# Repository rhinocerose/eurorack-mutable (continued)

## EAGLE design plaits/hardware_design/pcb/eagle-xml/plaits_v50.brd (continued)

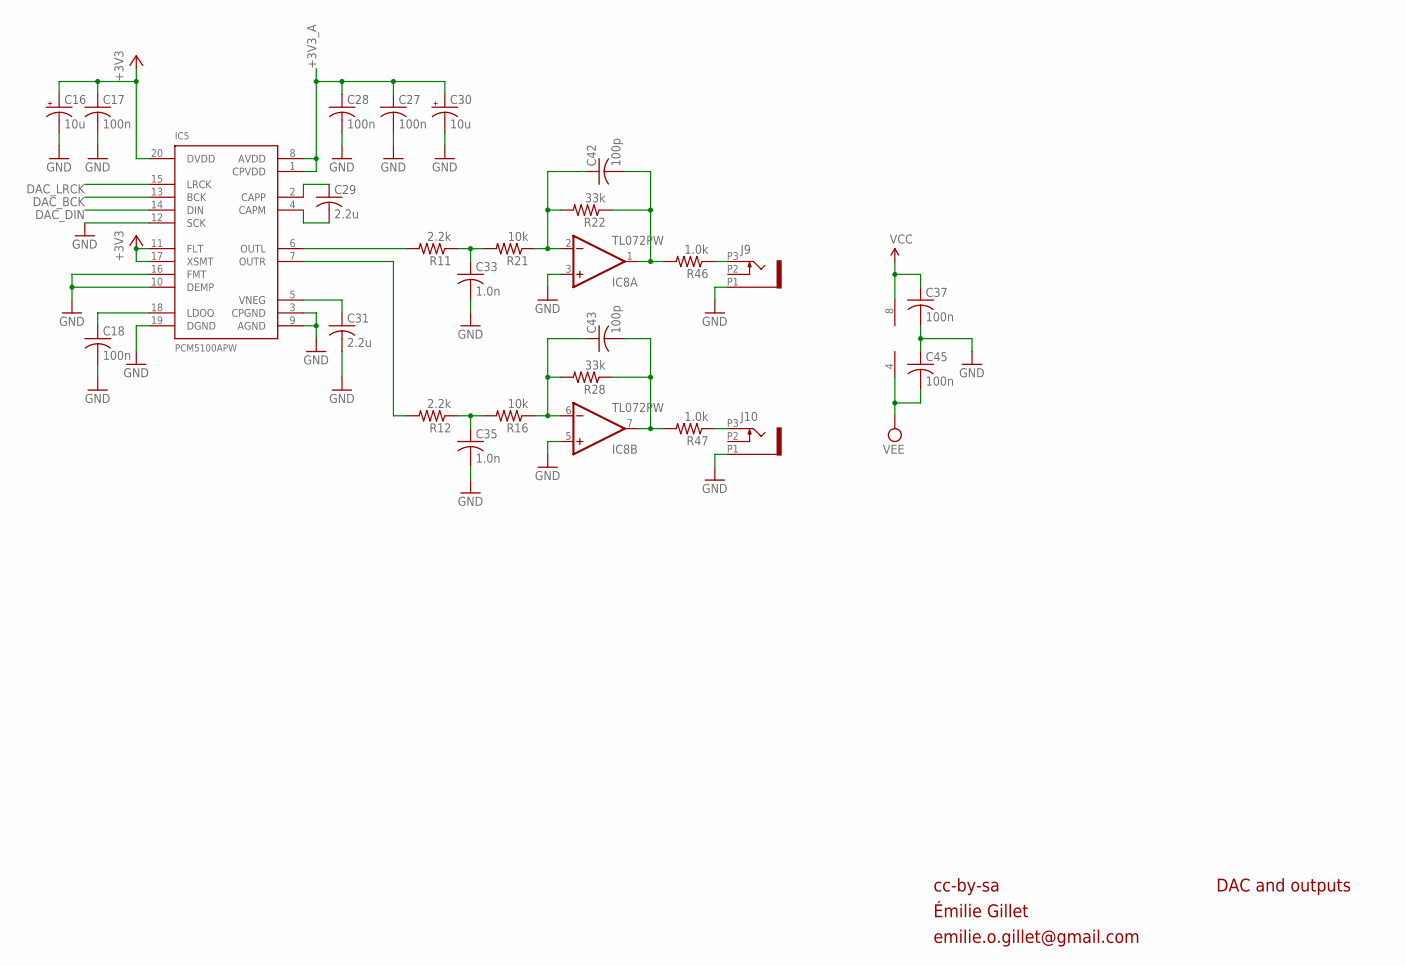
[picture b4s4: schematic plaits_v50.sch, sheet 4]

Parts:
C16, C30: 10u; PANASONIC_A
C17, C18, C27, C28, C37, C45: 100n; C0402
C29, C31: 2.2u; C0805
C33, C35: 1.0n; C0402
C42, C43: 100p; C0402
IC5: PCM5100APW; SSOP20
IC8: TL072PW; TSSOP08
J9, J10: PJ301_THONKICONN6; WQP_PJ_301M6
R11, R12: 2.2k; R0402
R16, R21: 10k; R0402
R22, R28: 33k; R0402
R46, R47: 1.0k; R0603

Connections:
+3V3: C16.+, C17.1, IC5.11 (FLT), IC5.17 (XSMT), IC5.20 (DVDD); also elsewhere on the board
+3V3_A: C27.1, C28.1, C30.+, IC5.1 (CPVDD), IC5.8 (AVDD); also elsewhere on the board
DAC_BCK: IC5.13 (BCK); also elsewhere on the board
DAC_DIN: IC5.14 (DIN); also elsewhere on the board
DAC_LRCK: IC5.15 (LRCK); also elsewhere on the board
GND: C16.-, C17.2, C18.2, C27.2, C28.2, C30.-, C31.2, C33.2, C35.2, C37.2, C45.1, IC5.3 (CPGND), IC5.9 (AGND), IC5.10 (DEMP), IC5.12 (SCK), IC5.16 (FMT), IC5.19 (DGND), IC8.3 (+IN), IC8.5 (+IN), J9.P1 (1), J10.P1 (1); also elsewhere on the board
unnamed: C29.1, IC5.2 (CAPP)
unnamed: C29.2, IC5.4 (CAPM)
unnamed: IC5.6 (OUTL), R11.2
unnamed: C33.1, R11.1, R21.2
unnamed: C35.1, R12.1, R16.2
unnamed: C31.1, IC5.5 (VNEG)
unnamed: C18.1, IC5.18 (LDOO)
unnamed: IC5.7 (OUTR), R12.2
unnamed: C43.1, IC8.6 (-IN), R16.1, R28.2
unnamed: C43.2, IC8.7 (OUT), R28.1, R47.2
unnamed: C42.1, IC8.2 (-IN), R21.1, R22.2
unnamed: C42.2, IC8.1 (OUT), R22.1, R46.2
unnamed: J9.P3 (3), R46.1
unnamed: J10.P3 (3), R47.1
VCC: C37.1, IC8.8 (V+); also elsewhere on the board
VEE: C45.2, IC8.4 (V-); also elsewhere on the board

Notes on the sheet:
cc-by-sa
DAC and outputs
Émilie Gillet
emilie.o.gillet@gmail.com

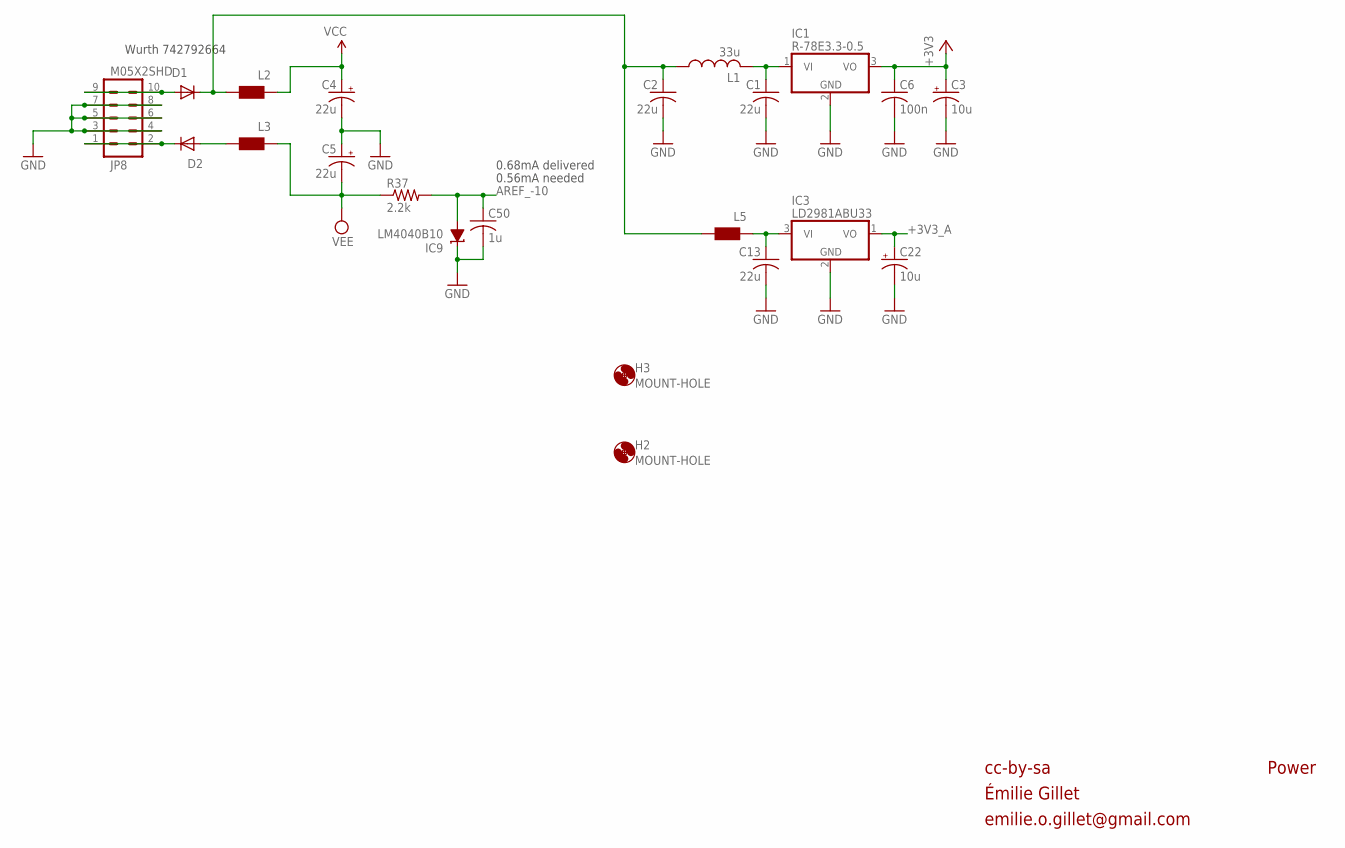
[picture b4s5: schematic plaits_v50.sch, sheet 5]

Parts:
C1, C2, C13: 22u; C1206
C3, C22: 10u; PANASONIC_A
C4, C5: 22u; PANASONIC_B
C6: 100n; C0402
C50: 1u; C0402
D1, D2: 1N5819HW; SOD123
H2, H3: MOUNT-HOLE; 3,0TINY
IC1: R-78E3.3-0.5; WE78
IC3: LD2981ABU33; SOT89
IC9: LM4040B10; DBZ_R-PDSO-G3
JP8: M05X2SHD; 2X5-SHROUDED
L1: 33u; L2012C
L2, L3, L5: WE-CBF_0603; 0603
R37: 2.2k; R0402

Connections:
+3V3: C3.+, C6.1, IC1.3 (VO); also elsewhere on the board
+3V3_A: C22.+, IC3.1 (VO); also elsewhere on the board
AREF_-10: C50.1, IC9.2 (A), R37.2; also elsewhere on the board
GND: C1.2, C2.2, C3.-, C4.-, C5.+, C6.2, C13.2, C22.-, C50.2, IC1.2 (GND), IC3.2 (GND), IC9.1 (C), JP8.3, JP8.4, JP8.5, JP8.6, JP8.7, JP8.8; also elsewhere on the board
unnamed: C1.1, IC1.1 (VI), L1.2
unnamed: D2.A, L3.2
unnamed: C2.1, D1.C, L1.1, L2.2, L5.2
unnamed: C13.1, IC3.3 (VI), L5.1
unnamed: D1.A, JP8.9, JP8.10
unnamed: D2.C, JP8.1, JP8.2
VCC: C4.+, L2.1; also elsewhere on the board
VEE: C5.-, L3.1, R37.1; also elsewhere on the board

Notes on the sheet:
cc-by-sa
Power
0.56mA needed
Wurth 742792664
0.68mA delivered
Émilie Gillet
emilie.o.gillet@gmail.com

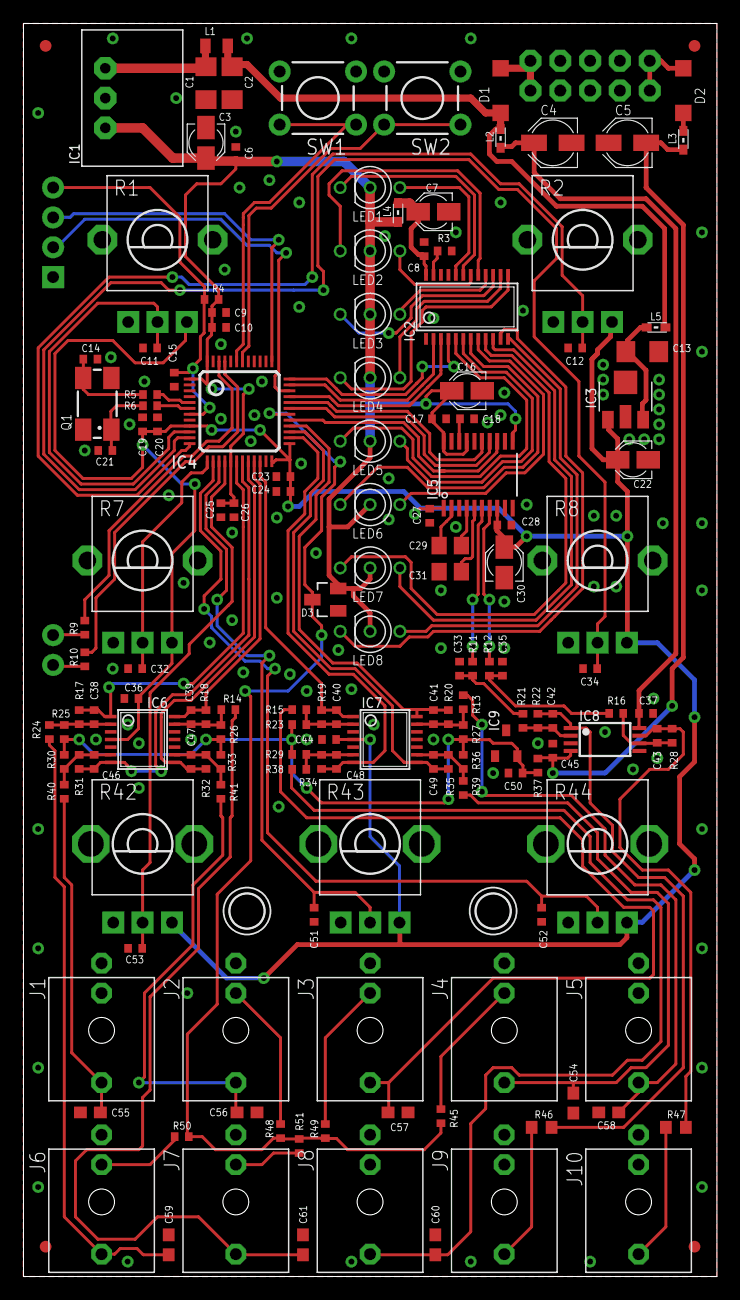
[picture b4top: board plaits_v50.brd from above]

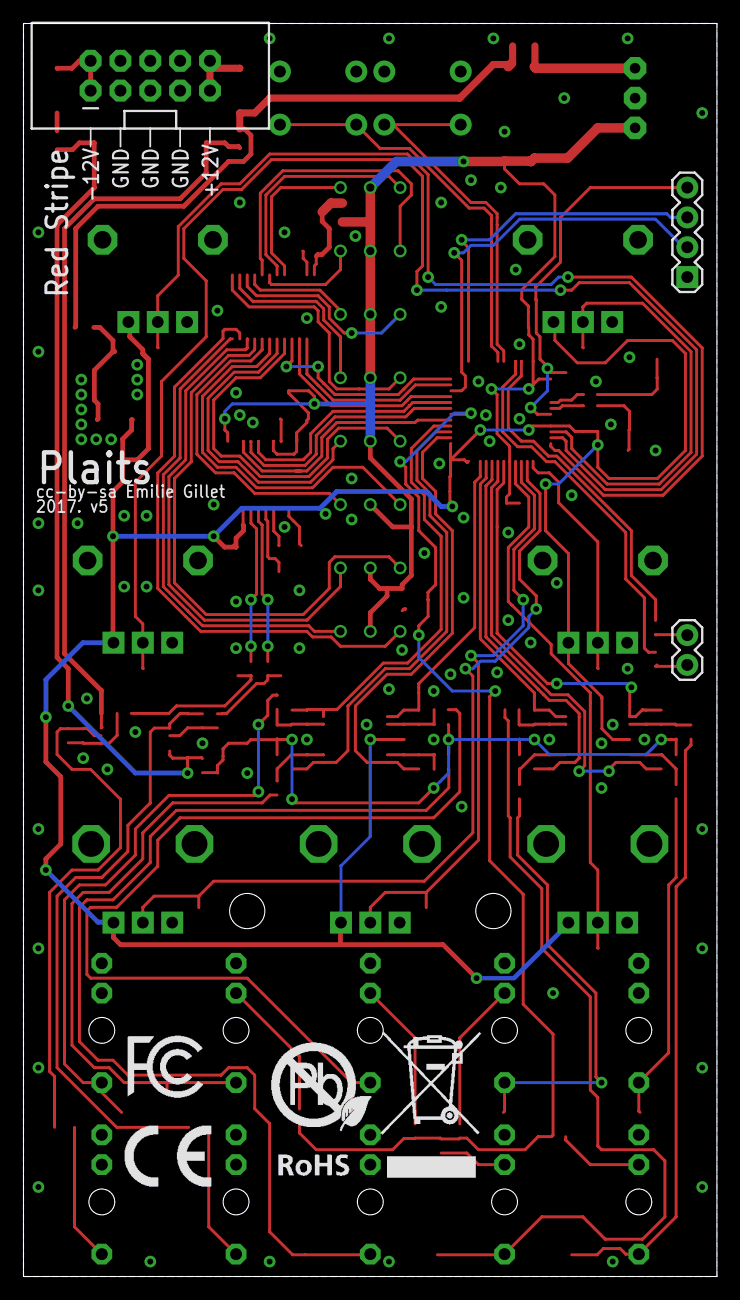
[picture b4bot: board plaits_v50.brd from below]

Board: 2 copper layers, 59.0 x 106.7 mm, 162 parts (6 on the bottom side), 100 nets.

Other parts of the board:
U$1: FCC_MEDIUM
U$2: ROHS_BIG
U$3: CE_MEDIUM

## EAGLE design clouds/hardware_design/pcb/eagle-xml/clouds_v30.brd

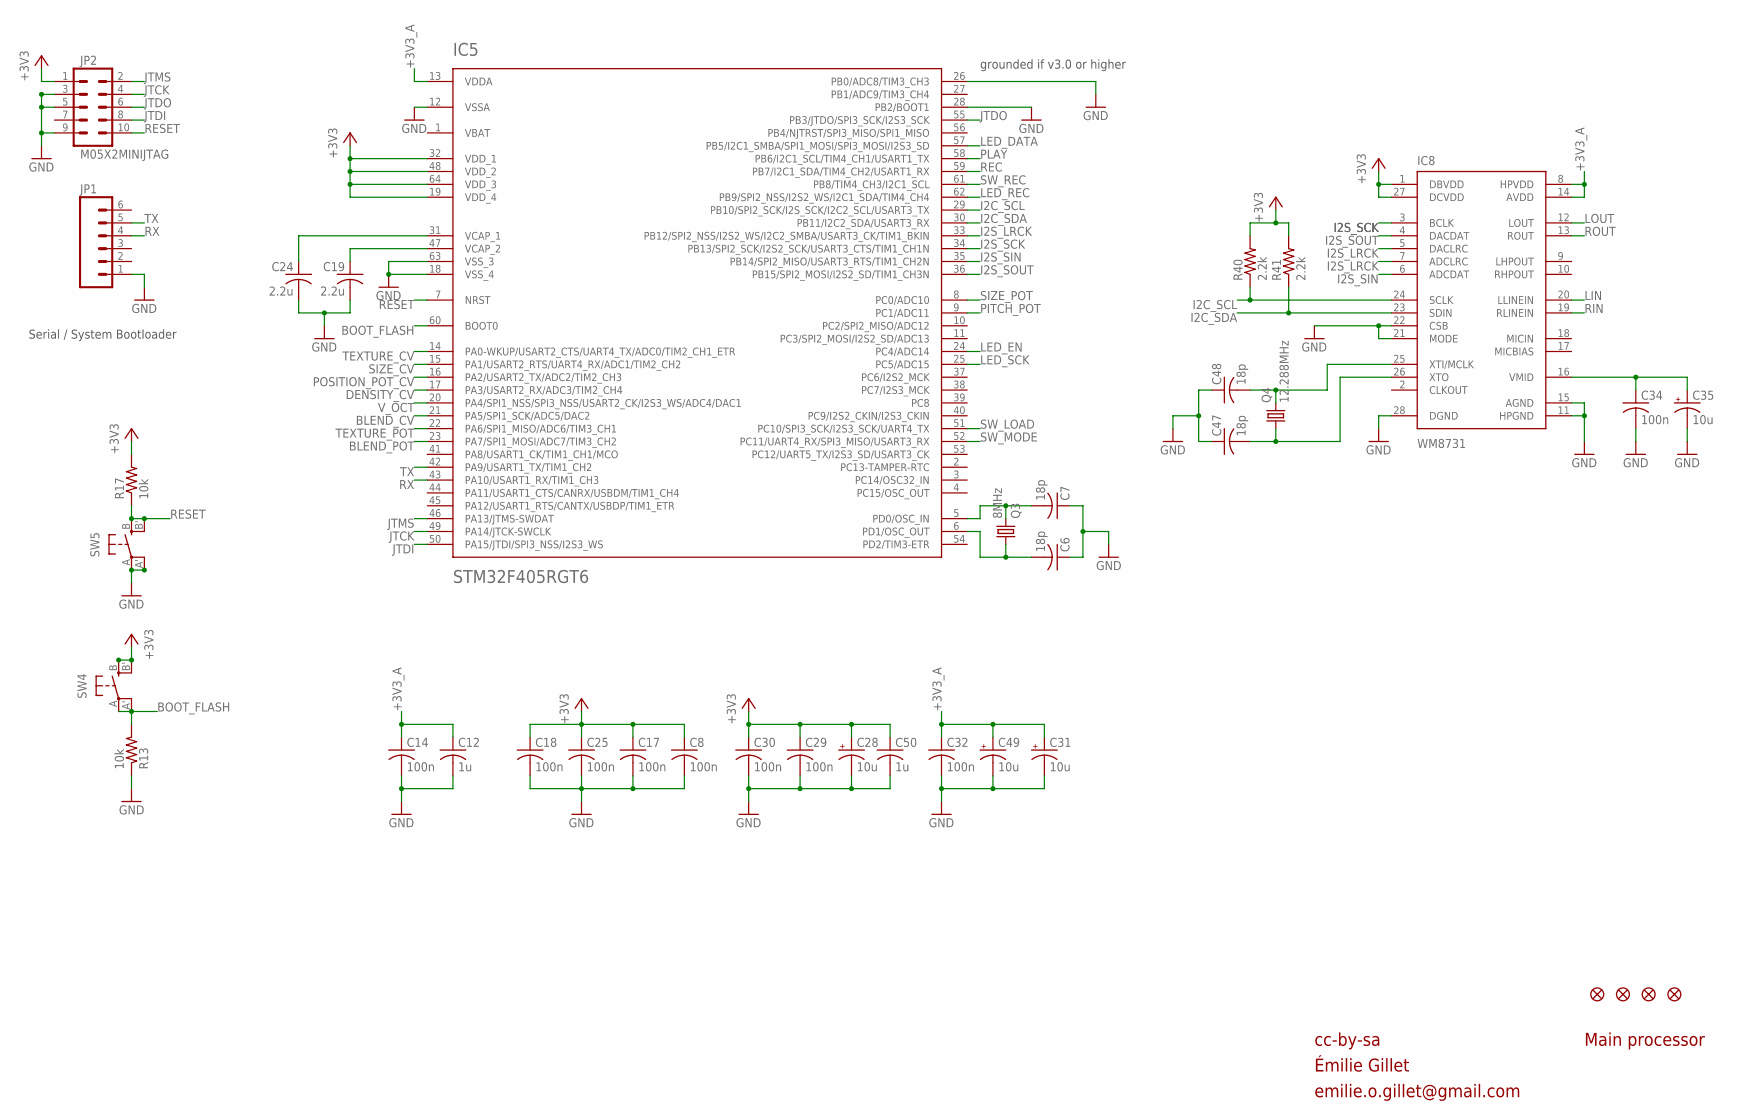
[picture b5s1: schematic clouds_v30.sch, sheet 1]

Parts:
C6, C7, C47, C48: 18p; C0603
C8, C14, C17, C18, C25, C29, C30, C32, C34: 100n; C0603
C12, C50: 1u; C0603
C19, C24: 2.2u; C0805
C28, C49: 10u; PANASONIC_A
C31, C35: 10u; PANASONIC_B
F1, F2, F3, F4: FIDUCIAL1X2; FIDUCIAL-1X2
IC5: STM32F405RGT6; TQFP-10X10-64
IC8: WM8731; SSOP28
JP1: M06SIP; 1X06
JP2: M05X2MINIJTAG; 2X5-1.27
Q3: 8MHz; HC49UP
Q4: 12.288MHz; HC49UP
R13, R17: 10k; R0603
R40, R41: 2.2k; R0603
SW4, SW5: EVQQ2; EVQ-Q2

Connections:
+3V3: C8.1, C17.1, C18.1, C25.1, C28.+, C29.1, C30.1, C50.1, IC5.19 (VDD_4), IC5.32 (VDD_1), IC5.48 (VDD_2), IC5.64 (VDD_3), IC8.1 (DBVDD), IC8.27 (DCVDD), JP2.1, R17.2, R40.2, R41.2, SW4.B (S), SW4.B' (S1); also elsewhere on the board
+3V3_A: C12.1, C14.1, C31.+, C32.1, C49.+, IC5.13 (VDDA), IC8.8 (HPVDD), IC8.14 (AVDD); also elsewhere on the board
BLEND_CV: IC5.21 (PA5/SPI1_SCK/ADC5/DAC2); also elsewhere on the board
BLEND_POT: IC5.23 (PA7/SPI1_MOSI/ADC7/TIM3_CH2); also elsewhere on the board
BOOT_FLASH: IC5.60 (BOOT0), R13.2, SW4.A, SW4.A' (P1)
DENSITY_CV: IC5.17 (PA3/USART2_RX/ADC3/TIM2_CH4); also elsewhere on the board
GND: C6.1, C7.1, C8.2, C12.2, C14.2, C17.2, C18.2, C19.2, C24.2, C25.2, C28.-, C29.2, C30.2, C31.-, C32.2, C34.2, C35.-, C47.1, C48.1, C49.-, C50.2, IC5.12 (VSSA), IC5.18 (VSS_4), IC5.26 (PB0/ADC8/TIM3_CH3), IC5.28 (PB2/BOOT1), IC5.63 (VSS_3), IC8.11 (HPGND), IC8.15 (AGND), IC8.21 (MODE), IC8.22 (CSB), IC8.28 (DGND), JP1.1, JP2.3, JP2.5, JP2.9, R13.1, SW5.A, SW5.A' (P1); also elsewhere on the board
I2C_SCL: IC5.29 (PB10/SPI2_SCK/I2S_SCK/I2C2_SCL/USART3_TX), IC8.24 (SCLK), R40.1
I2C_SDA: IC5.30 (PB11/I2C2_SDA/USART3_RX), IC8.23 (SDIN), R41.1
I2S_LRCK: IC5.33 (PB12/SPI2_NSS/I2S2_WS/I2C2_SMBA/USART3_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), IC8.5 (DACLRC), IC8.7 (ADCLRC)
I2S_SCK: IC5.34 (PB13/SPI2_SCK/I2S2_SCK/USART3_CTS/TIM1_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), IC8.3 (BCLK)
I2S_SIN: IC5.35 (PB14/SPI2_MISO/USART3_RTS/TIM1_CH2N), IC8.6 (ADCDAT)
I2S_SOUT: IC5.36 (PB15/SPI2_MOSI/I2S2_SD/TIM1_CH3N), IC8.4 (DACDAT)
JTCK: IC5.49 (PA14/JTCK-SWCLK), JP2.4
JTDI: IC5.50 (PA15/JTDI/SPI3_NSS/I2S3_WS), JP2.8
JTDO: IC5.55 (PB3/JTDO/SPI3_SCK/I2S3_SCK), JP2.6
JTMS: IC5.46 (PA13/JTMS-SWDAT), JP2.2
LED_DATA: IC5.57 (PB5/I2C1_SMBA/SPI1_MOSI/SPI3_MOSI/I2S3_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); also elsewhere on the board
LED_EN: IC5.24 (PC4/ADC14); also elsewhere on the board
LED_REC: IC5.62 (PB9/SPI2_NSS/I2S2_WS/I2C1_SDA/TIM4_CH4); also elsewhere on the board
LED_SCK: IC5.25 (PC5/ADC15); also elsewhere on the board
LIN: IC8.20 (LLINEIN); also elsewhere on the board
LOUT: IC8.12 (LOUT); also elsewhere on the board
unnamed: C7.2, IC5.5 (PD0/OSC_IN), Q3.2
unnamed: C6.2, IC5.6 (PD1/OSC_OUT), Q3.1
unnamed: C19.1, IC5.47 (VCAP_2)
unnamed: C34.1, C35.+, IC8.16 (VMID)
unnamed: C24.1, IC5.31 (VCAP_1)
unnamed: C47.2, IC8.26 (XTO), Q4.1
unnamed: C48.2, IC8.25 (XTI/MCLK), Q4.2
PITCH_POT: IC5.9 (PC1/ADC11); also elsewhere on the board
PLAY: IC5.58 (PB6/I2C1_SCL/TIM4_CH1/USART1_TX); also elsewhere on the board
POSITION_POT_CV: IC5.16 (PA2/USART2_TX/ADC2/TIM2_CH3); also elsewhere on the board
REC: IC5.59 (PB7/I2C1_SDA/TIM4_CH2/USART1_RX); also elsewhere on the board
RESET: IC5.7 (NRST), JP2.10, R17.1, SW5.B (S), SW5.B' (S1)
RIN: IC8.19 (RLINEIN); also elsewhere on the board
ROUT: IC8.13 (ROUT); also elsewhere on the board
RX: IC5.43 (PA10/USART1_RX/TIM1_CH3), JP1.4
SIZE_CV: IC5.15 (PA1/USART2_RTS/UART4_RX/ADC1/TIM2_CH2); also elsewhere on the board
SIZE_POT: IC5.8 (PC0/ADC10); also elsewhere on the board
SW_LOAD: IC5.51 (PC10/SPI3_SCK/I2S3_SCK/UART4_TX); also elsewhere on the board
SW_MODE: IC5.52 (PC11/UART4_RX/SPI3_MISO/USART3_RX); also elsewhere on the board
SW_REC: IC5.61 (PB8/TIM4_CH3/I2C1_SCL); also elsewhere on the board
TEXTURE_CV: IC5.14 (PA0-WKUP/USART2_CTS/UART4_TX/ADC0/TIM2_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); also elsewhere on the board
TEXTURE_POT: IC5.22 (PA6/SPI1_MISO/ADC6/TIM3_CH1); also elsewhere on the board
TX: IC5.42 (PA9/USART1_TX/TIM1_CH2), JP1.5
VBAT: IC5.1 (VBAT)
V_OCT: IC5.20 (PA4/SPI1_NSS/SPI3_NSS/USART2_CK/I2S3_WS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); also elsewhere on the board

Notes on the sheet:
cc-by-sa
Main processor
Serial / System Bootloader
grounded if v3.0 or higher
Émilie Gillet
emilie.o.gillet@gmail.com

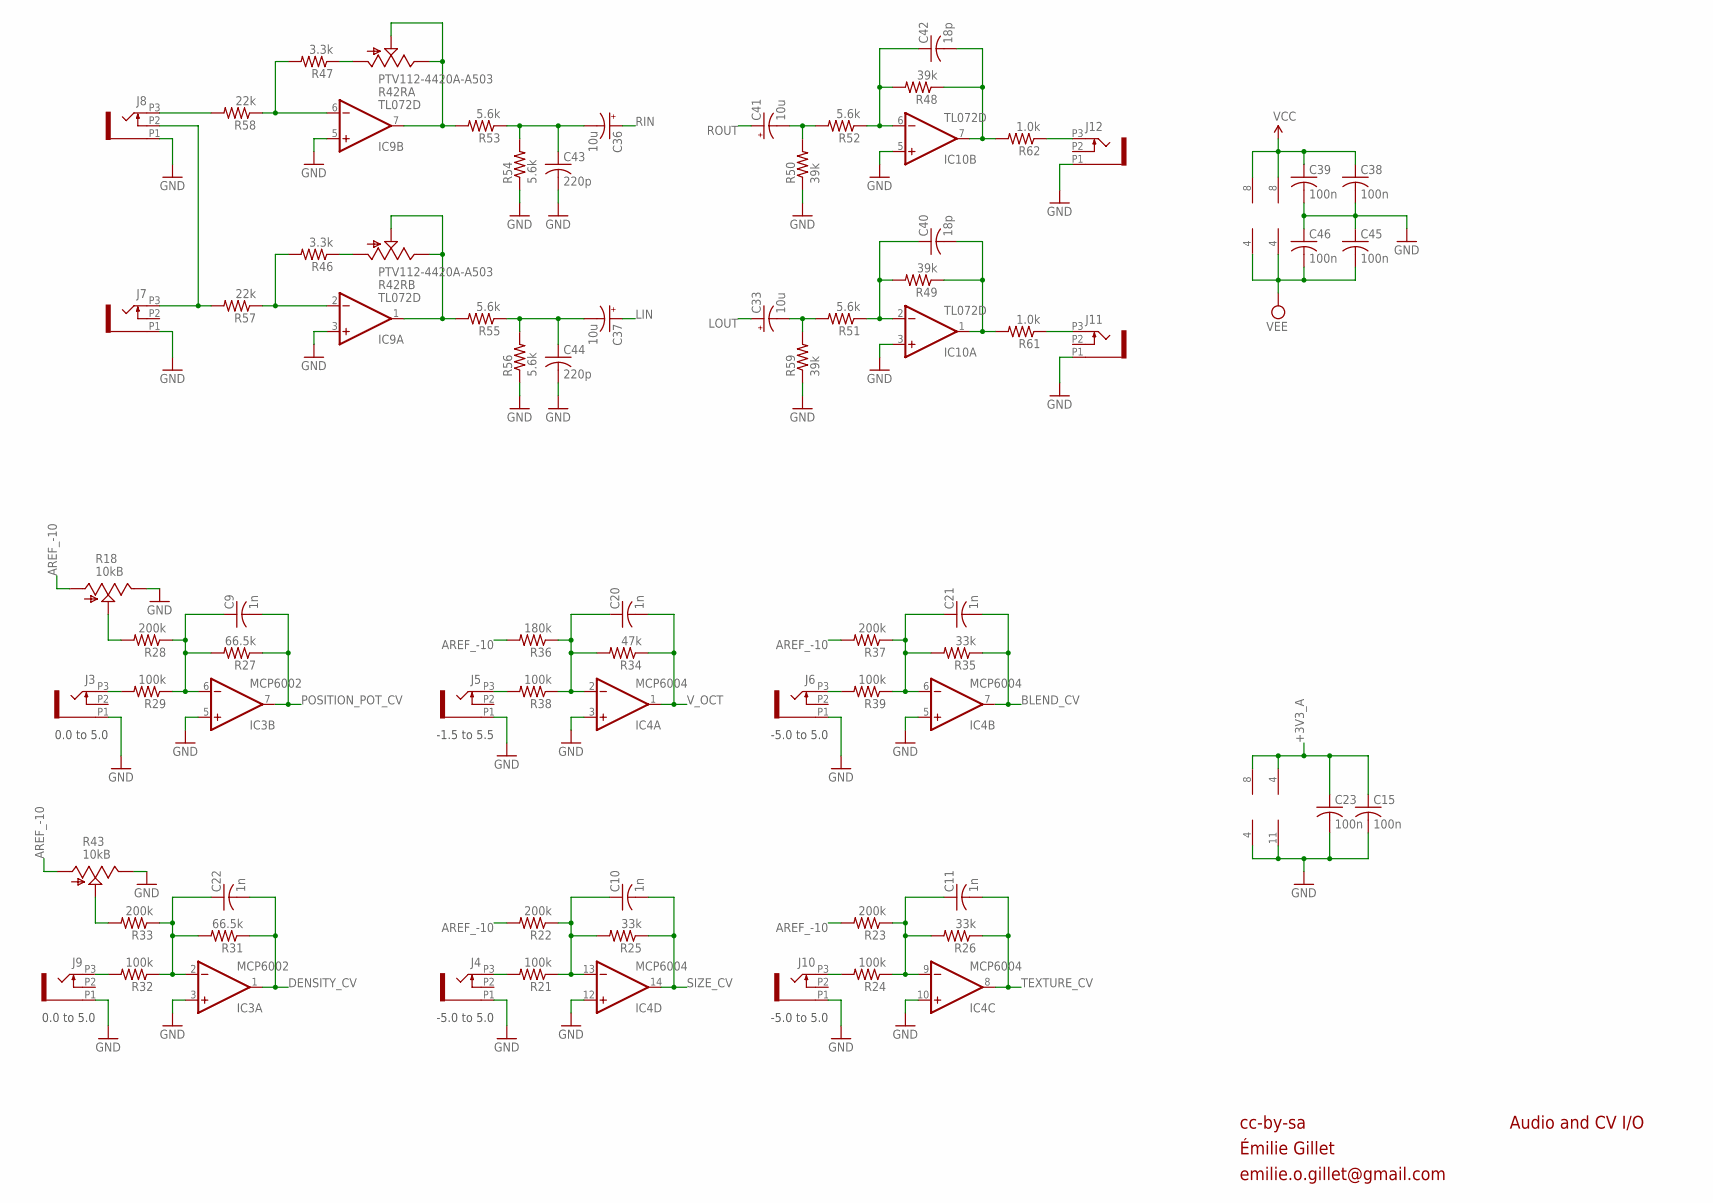
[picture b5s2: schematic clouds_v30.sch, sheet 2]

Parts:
C9, C10, C11, C20, C21, C22: 1n; C0603
C15, C23, C38, C39, C45, C46: 100n; C0603
C33, C36, C37, C41: 10u; PANASONIC_B
C40, C42: 18p; C0603
C43, C44: 220p; C0603
IC3: MCP6002; SO08
IC4: MCP6004; SO14
IC9, IC10: TL072D; SO08
J3, J4, J5, J6, J7, J8, J9, J10, J11, J12: PJ301_THONKICONN6; WQP_PJ_301M6
R18, R43: 10kB; ALPS_POT_VERTICAL_PS
R21, R24, R29, R32, R38, R39: 100k; R0603
R22, R23, R28, R33, R37: 200k; R0603
R25, R26, R35: 33k; R0603
R27, R31: 66.5k; R0603
R34: 47k; R0603
R36: 180k; R0603
R42: PTV112-4420A-A503; BOURNS_PTV112
R46, R47: 3.3k; R0603
R48, R49, R50, R59: 39k; R0603
R51, R52, R53, R54, R55, R56: 5.6k; R0603
R57, R58: 22k; R0603
R61, R62: 1.0k; R0603

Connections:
+3V3_A: C15.1, C23.1, IC3.8 (V+), IC4.4 (V+); also elsewhere on the board
AREF_-10: R18.P$3 (A), R22.2, R23.2, R36.2, R37.2, R43.P$3 (A); also elsewhere on the board
BLEND_CV: C21.2, IC4.7 (OUT), R35.1; also elsewhere on the board
DENSITY_CV: C22.2, IC3.1 (OUT), R31.1; also elsewhere on the board
GND: C15.2, C23.2, C38.2, C39.2, C43.2, C44.2, C45.1, C46.1, IC3.3 (+IN), IC3.4 (V-), IC3.5 (+IN), IC4.3 (+IN), IC4.5 (+IN), IC4.10 (+IN), IC4.11 (V-), IC4.12 (+IN), IC9.3 (+IN), IC9.5 (+IN), IC10.3 (+IN), IC10.5 (+IN), J3.P1 (1), J4.P1 (1), J5.P1 (1), J6.P1 (1), J7.P1 (1), J8.P1 (1), J9.P1 (1), J10.P1 (1), J11.P1 (1), J12.P1 (1), R18.P$1 (E), R43.P$1 (E), R50.1, R54.1, R56.1, R59.1; also elsewhere on the board
LIN: C37.+; also elsewhere on the board
LOUT: C33.+; also elsewhere on the board
LOUT_JACK: J11.P3 (3), R61.1
unnamed: J4.P3 (3), R21.2
unnamed: C10.1, IC4.13 (-IN), R21.1, R22.1, R25.2
unnamed: J10.P3 (3), R24.2
unnamed: C11.1, IC4.9 (-IN), R23.1, R24.1, R26.2
unnamed: J6.P3 (3), R39.2
unnamed: J5.P3 (3), R38.2
unnamed: C20.1, IC4.2 (-IN), R34.2, R36.1, R38.1
unnamed: J9.P3 (3), R32.2
unnamed: C21.1, IC4.6 (-IN), R35.2, R37.1, R39.1
unnamed: C37.-, C44.1, R55.1, R56.2
unnamed: J8.P3 (3), R58.2
unnamed: J7.P3 (3), J8.P2 (2), R57.2
unnamed: C36.-, C43.1, R53.1, R54.2
unnamed: C41.-, R50.2, R52.2
unnamed: C22.1, IC3.2 (-IN), R31.2, R32.1, R33.1
unnamed: C42.1, IC10.6 (-IN), R48.2, R52.1
unnamed: R33.2, R43.P$2 (S)
unnamed: J3.P3 (3), R29.2
unnamed: C42.2, IC10.7 (OUT), R48.1, R62.2
unnamed: C9.1, IC3.6 (-IN), R27.2, R28.1, R29.1
unnamed: C33.-, R51.2, R59.2
unnamed: C40.1, IC10.2 (-IN), R49.2, R51.1
unnamed: C40.2, IC10.1 (OUT), R49.1, R61.2
unnamed: R18.P$2 (S), R28.2
unnamed: IC9.7 (OUT), R42.2P (S), R42.3P (E), R53.2
unnamed: IC9.1 (OUT), R42.2 (S), R42.3 (E), R55.2
unnamed: R42.1P (A), R47.1
unnamed: R42.1 (A), R46.1
unnamed: IC9.6 (-IN), R47.2, R58.1
unnamed: IC9.2 (-IN), R46.2, R57.1
POSITION_POT_CV: C9.2, IC3.7 (OUT), R27.1; also elsewhere on the board
RIN: C36.+; also elsewhere on the board
ROUT: C41.+; also elsewhere on the board
ROUT_JACK: J12.P3 (3), R62.1
SIZE_CV: C10.2, IC4.14 (OUT), R25.1; also elsewhere on the board
TEXTURE_CV: C11.2, IC4.8 (OUT), R26.1; also elsewhere on the board
VCC: C38.1, C39.1, IC9.8 (V+), IC10.8 (V+); also elsewhere on the board
VEE: C45.2, C46.2, IC9.4 (V-), IC10.4 (V-); also elsewhere on the board
V_OCT: C20.2, IC4.1 (OUT), R34.1; also elsewhere on the board

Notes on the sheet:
cc-by-sa
Audio and CV I/O
0.0 to 5.0
-1.5 to 5.5
-5.0 to 5.0
Émilie Gillet
emilie.o.gillet@gmail.com

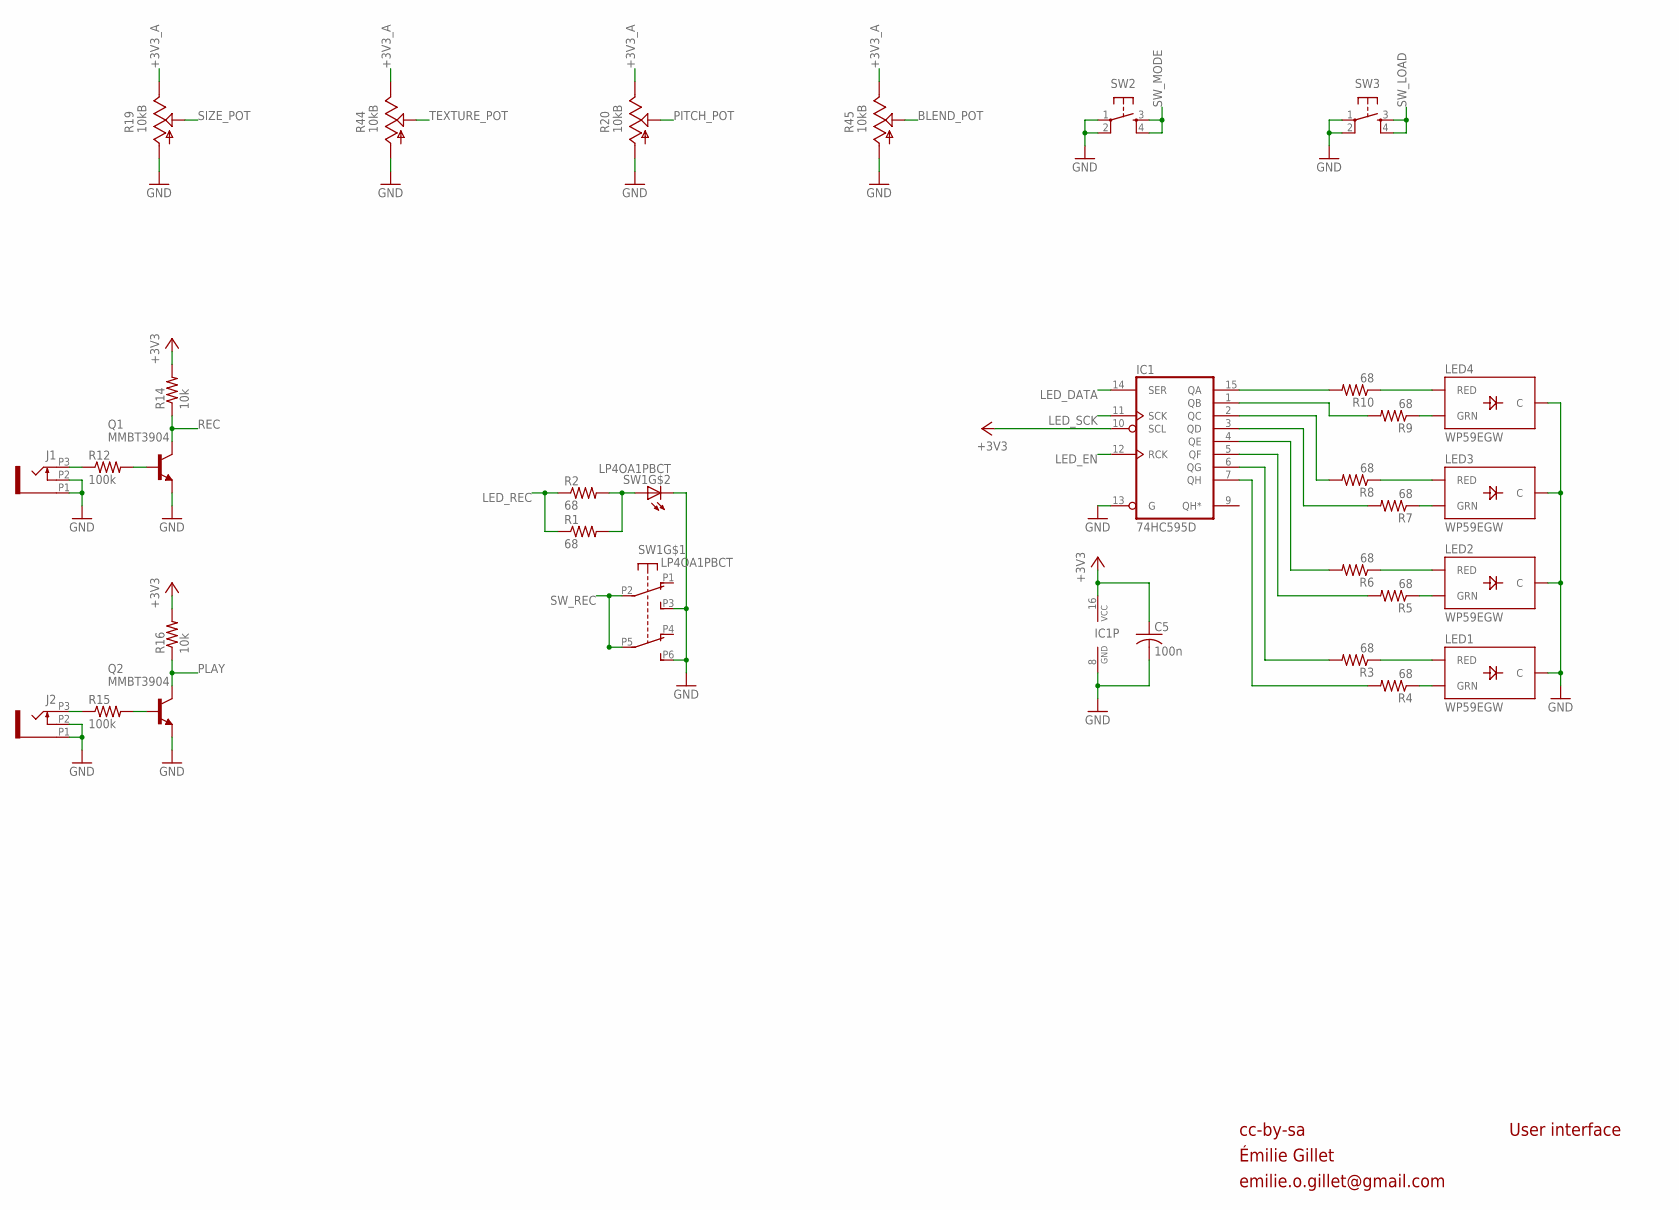
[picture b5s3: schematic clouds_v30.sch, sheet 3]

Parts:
C5: 100n; C0603
IC1: 74HC595D; SO16
J1, J2: PJ301_THONKICONN6; WQP_PJ_301M6
LED1, LED2, LED3, LED4: WP59EGW; LED-BICOLOR-THROUGHHOLE-5MM
Q1, Q2: MMBT3904; SOT23-BEC
R1, R2, R3, R4, R5, R6, R7, R8, R9, R10: 68; R0603
R12, R15: 100k; R0603
R14, R16: 10k; R0603
R19, R20, R44, R45: 10kB; ALPS_POT_VERTICAL_PS
SW1: LP4OA1PBCT
SW2, SW3: TAC_SWITCHPTH; TACTILE-PTH

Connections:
+3V3: C5.1, IC1.10 (SCL), IC1.16 (VCC), R14.2, R16.2; also elsewhere on the board
+3V3_A: R19.P$1 (E), R20.P$1 (E), R44.P$1 (E), R45.P$1 (E); also elsewhere on the board
BLEND_POT: R45.P$2 (S); also elsewhere on the board
GND: C5.2, IC1.8 (GND), IC1.13 (G), J1.P1 (1), J1.P2 (2), J2.P1 (1), J2.P2 (2), LED1.2 (C), LED2.2 (C), LED3.2 (C), LED4.2 (C), Q1.E, Q2.E, R19.P$3 (A), R20.P$3 (A), R44.P$3 (A), R45.P$3 (A), SW1.L2, SW1.P3 (A3), SW1.P6 (B3), SW2.1, SW2.2, SW3.1, SW3.2; also elsewhere on the board
LED_DATA: IC1.14 (SER); also elsewhere on the board
LED_EN: IC1.12 (RCK); also elsewhere on the board
LED_REC: R1.1, R2.1; also elsewhere on the board
LED_SCK: IC1.11 (SCK); also elsewhere on the board
unnamed: LED4.3 (GRN), R9.1
unnamed: LED4.1 (RED), R10.1
unnamed: LED3.1 (RED), R8.1
unnamed: LED3.3 (GRN), R7.1
unnamed: LED2.1 (RED), R6.1
unnamed: J2.P3 (3), R15.1
unnamed: Q2.B, R15.2
unnamed: R1.2, R2.2, SW1.L1
unnamed: LED2.3 (GRN), R5.1
unnamed: LED1.1 (RED), R3.1
unnamed: LED1.3 (GRN), R4.1
unnamed: IC1.15 (QA), R10.2
unnamed: IC1.1 (QB), R9.2
unnamed: IC1.2 (QC), R8.2
unnamed: IC1.3 (QD), R7.2
unnamed: IC1.4 (QE), R6.2
unnamed: IC1.5 (QF), R5.2
unnamed: IC1.6 (QG), R3.2
unnamed: IC1.7 (QH), R4.2
unnamed: J1.P3 (3), R12.1
unnamed: Q1.B, R12.2
PITCH_POT: R20.P$2 (S); also elsewhere on the board
PLAY: Q2.C, R16.1; also elsewhere on the board
REC: Q1.C, R14.1; also elsewhere on the board
SIZE_POT: R19.P$2 (S); also elsewhere on the board
SW_LOAD: SW3.3, SW3.4; also elsewhere on the board
SW_MODE: SW2.3, SW2.4; also elsewhere on the board
SW_REC: SW1.P2 (A2), SW1.P5 (B2); also elsewhere on the board
TEXTURE_POT: R44.P$2 (S); also elsewhere on the board

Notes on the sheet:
cc-by-sa
User interface
Émilie Gillet
emilie.o.gillet@gmail.com

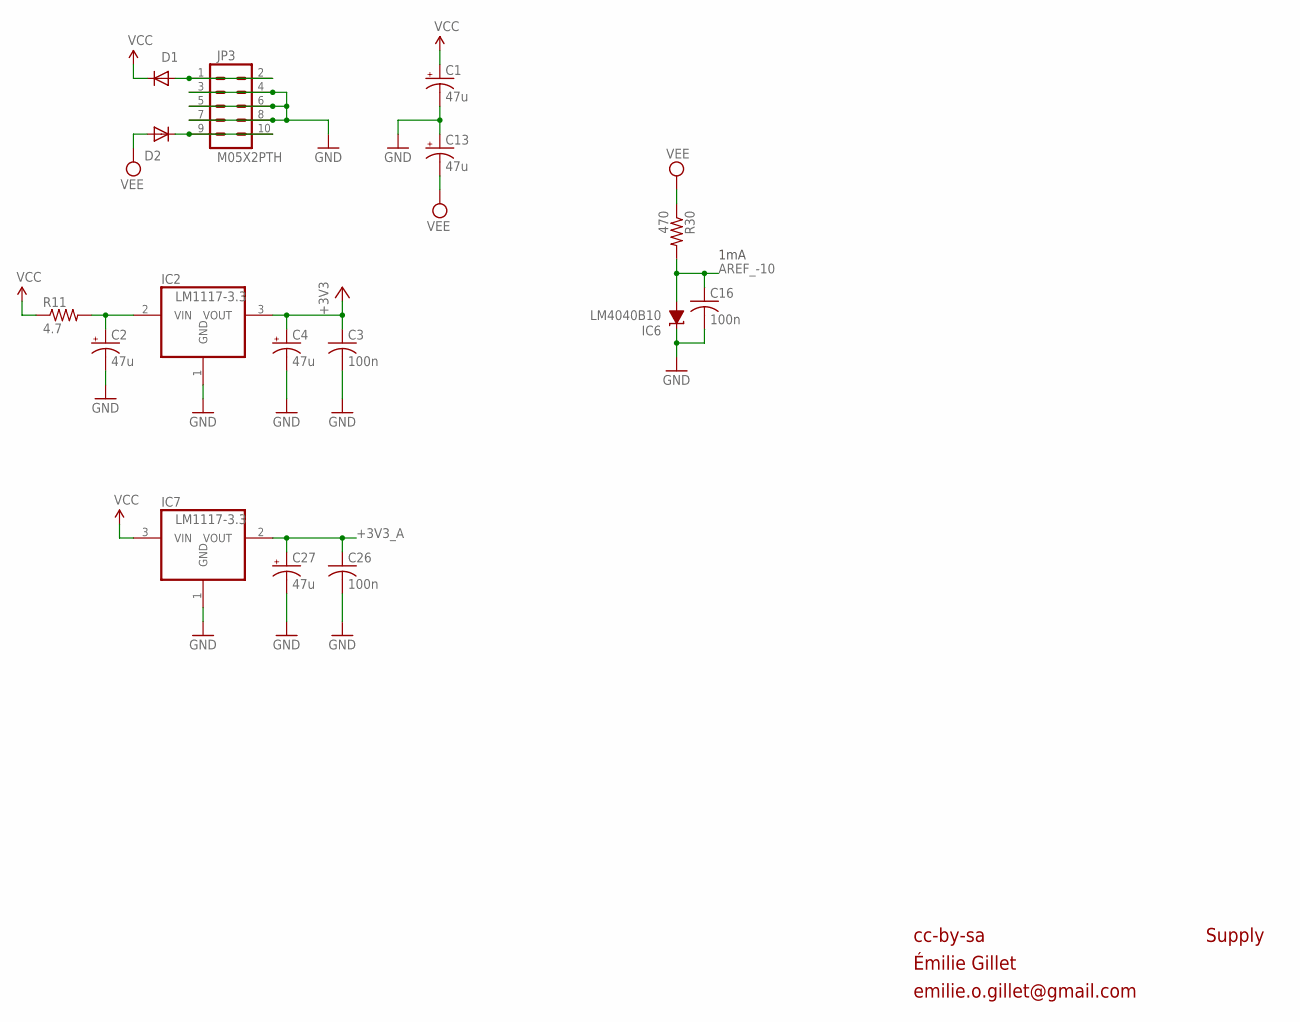
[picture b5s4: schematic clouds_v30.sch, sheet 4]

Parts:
C1, C2, C4, C13, C27: 47u; PANASONIC_D
C3, C16, C26: 100n; C0603
D1, D2: 1N5819HW; SOD123
IC2: LM1117-3.3; TO252
IC6: LM4040B10; DBZ_R-PDSO-G3
IC7: LM1117-3.3; SOT223
JP3: M05X2PTH; AVR_ICSP
R11: 4.7; R1206
R30: 470; R0603

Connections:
+3V3: C3.1, C4.+, IC2.3 (VOUT); also elsewhere on the board
+3V3_A: C26.1, C27.+, IC7.2 (VOUT); also elsewhere on the board
AREF_-10: C16.1, IC6.2 (A), R30.2; also elsewhere on the board
GND: C1.-, C2.-, C3.2, C4.-, C13.+, C16.2, C26.2, C27.-, IC2.1 (GND), IC6.1 (C), IC7.1 (GND), JP3.3, JP3.4, JP3.5, JP3.6, JP3.7, JP3.8; also elsewhere on the board
unnamed: C2.+, IC2.2 (VIN), R11.2
unnamed: D1.A, JP3.1, JP3.2
unnamed: D2.C, JP3.9, JP3.10
VCC: C1.+, D1.C, IC7.3 (VIN), R11.1; also elsewhere on the board
VEE: C13.-, D2.A, R30.1; also elsewhere on the board

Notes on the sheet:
1mA
cc-by-sa
Supply
Émilie Gillet
emilie.o.gillet@gmail.com

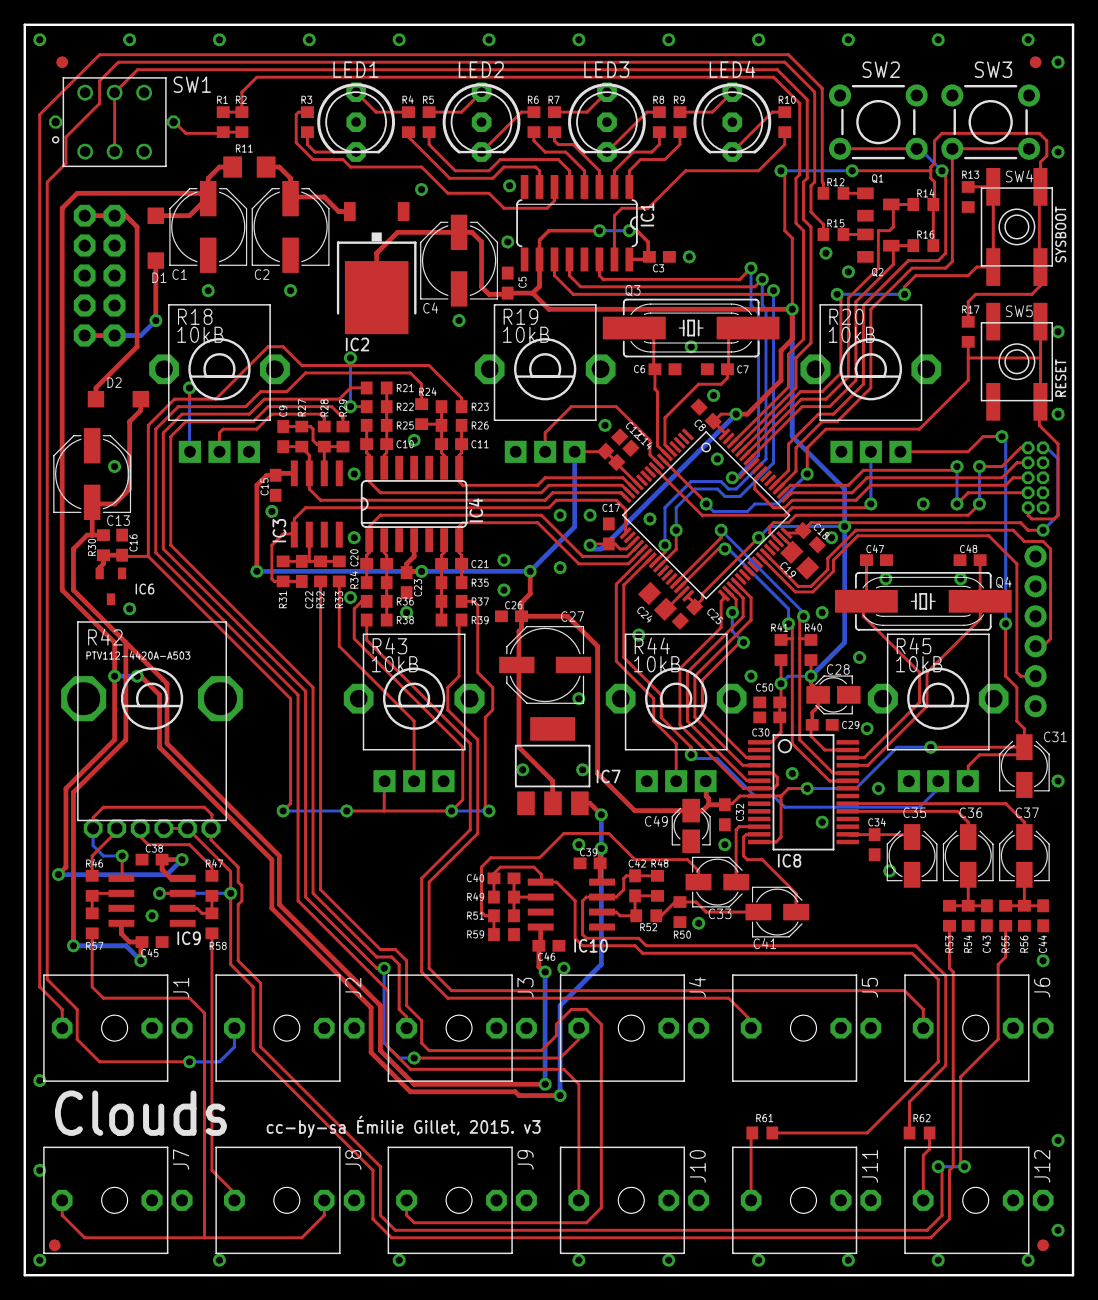
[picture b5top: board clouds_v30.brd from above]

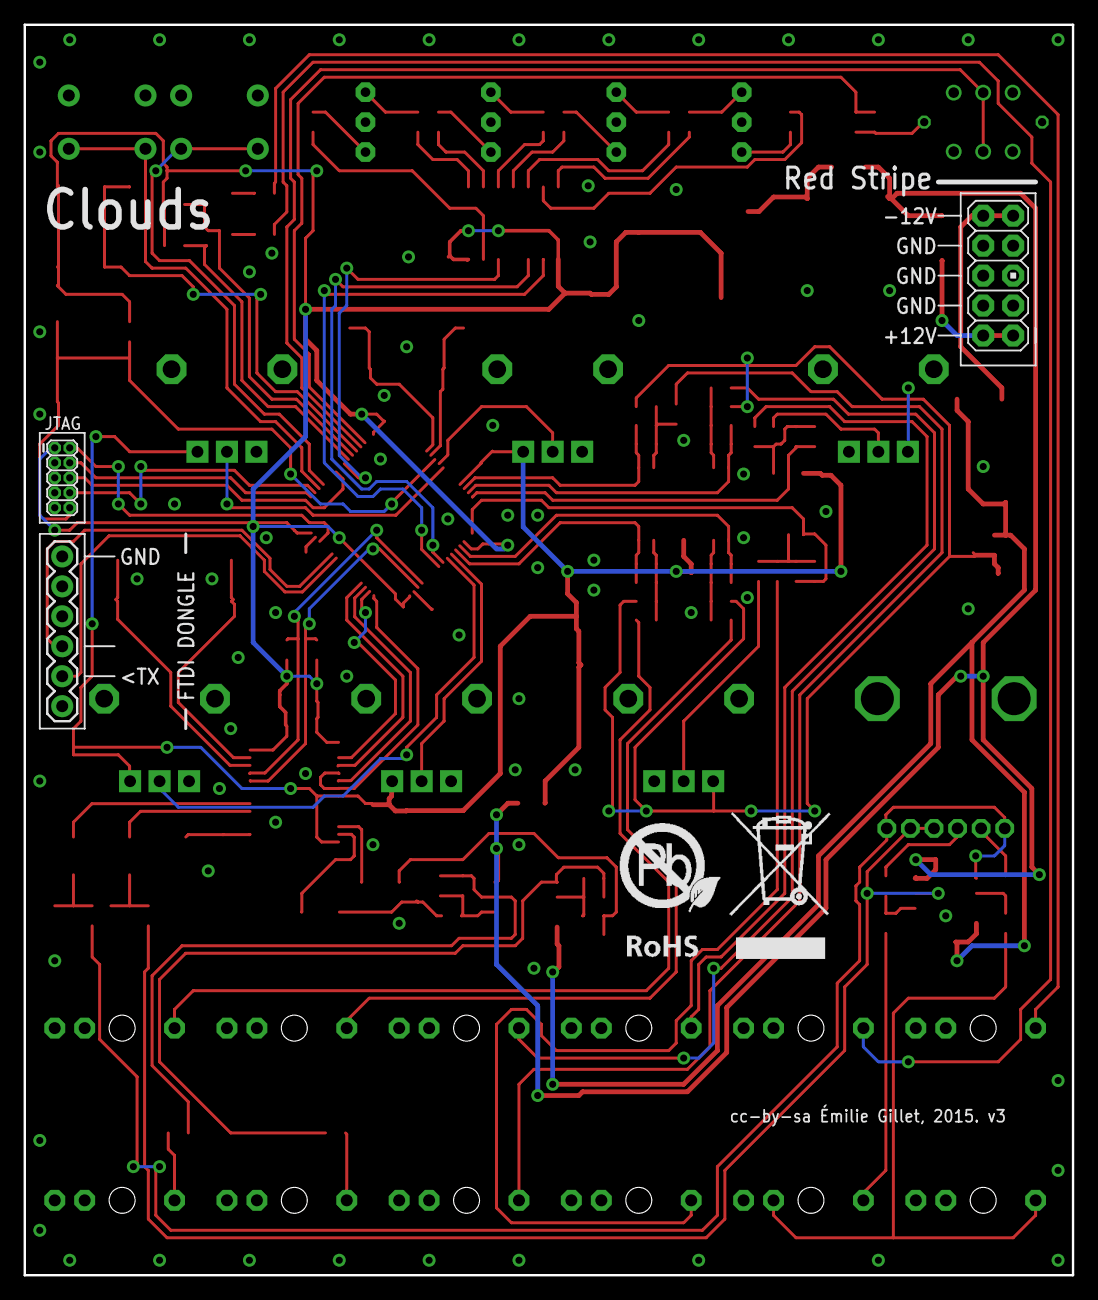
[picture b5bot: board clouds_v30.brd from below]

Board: 2 copper layers, 88.9 x 106.0 mm, 156 parts (4 on the bottom side), 106 nets.

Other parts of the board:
U$2: ROHS_BIG
